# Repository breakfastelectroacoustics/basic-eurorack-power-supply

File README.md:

# Basic Eurorack Power Supply

This power supply derives +12 V, -12 V and +5 V from 12 V AC. It is intended as a cheap and simple bipolar (plus 5 V) power supply for modular synthesizers and general test setups.

The double-sided PCB layout is very straightforward. One of the AC inputs connected on the left will be referenced as GND. The regulated DC output on the right will be relative to this reference.

To keep it as simple as possible the circuit only contains essential components. 7812, 7912 and 7805 linear regulators are used in their basic fixed-voltage configuration (as suggested in the datasheets and used in many designs e.g. from [MFOS](http://musicfromouterspace.com/analogsynth_new/WALLWARTSUPPLY/WALLWARTSUPPLY.php) and [ModularSynth.ru](http://www.modularsynth.ru/en/diy/low_cost_psu/)).

The diodes, voltage regulators and the AC supply used determine the amount of current this power supply can provide. Depending on the application additional fuses or protection diodes are recommended. If heatsinks are used on the linear regulators, they must not touch each other.

Components listed on the BOM are only loosely defined. They have to be specified/adapted to fit individual requirements (with preferably generous safety margins, e.g. capacitors rated 35 V for 12-15 V AC input).

Dimensions: 99.06 x 41.91 mm

Mounting hole pattern: 50.8 (25.4) x 35.56 mm (~3 mm hole diameter)

The PCB files are licensed under a [Creative Commons Attribution-NonCommercial-ShareAlike 4.0 International License](https://creativecommons.org/licenses/by-nc-sa/4.0/).

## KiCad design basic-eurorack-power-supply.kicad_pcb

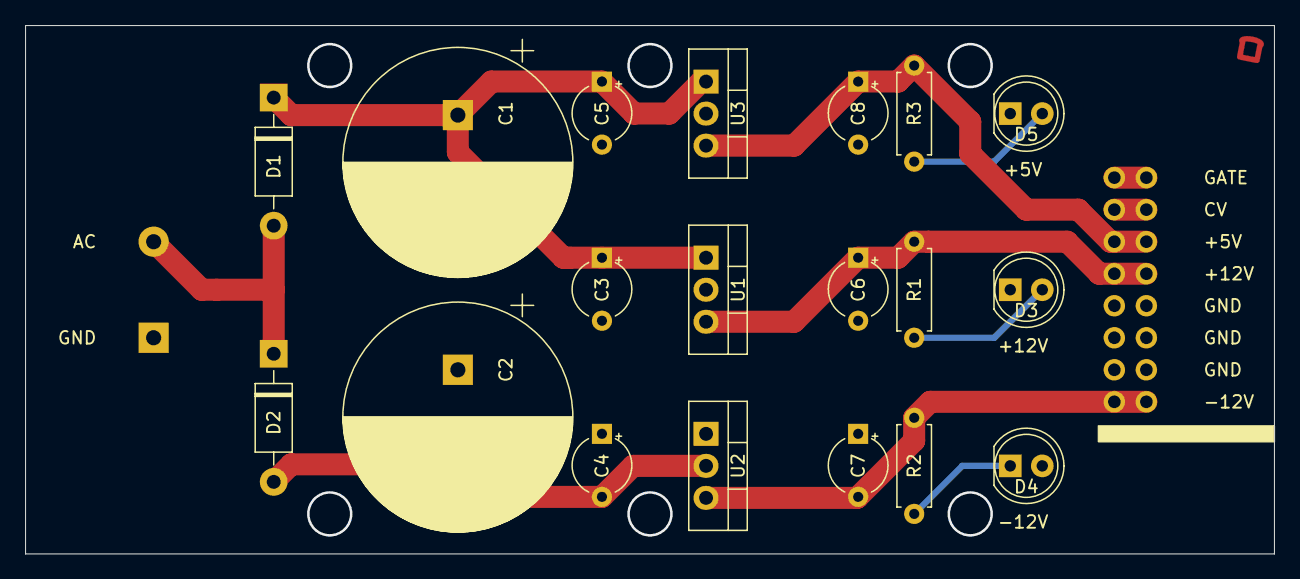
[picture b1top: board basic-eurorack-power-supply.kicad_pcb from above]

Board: 2 copper layers, 99.1 x 41.9 mm, 19 parts (0 on the bottom side), 10 nets.

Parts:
C1, C2: 4700u; CP_Radial_D18.0mm_P7.50mm
C3, C4, C5, C6, C7, C8: 1u; CP_Radial_Tantal_D4.5mm_P5.00mm
D1, D2: 1N4001; D_DO-41_SOD81_P10.16mm_Horizontal
D3, D4, D5: LED; LED_D5.0mm
R1, R2, R3: R; R_Axial_DIN0207_L6.3mm_D2.5mm_P7.62mm_Horizontal
U1: L7812; TO-220-3_Vertical
U2: L7912; TO-220-3_Vertical
U3: L7805; TO-220-3_Vertical

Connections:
+5V: C8.1, R3.1, U3.3
+12V: C6.1, R1.2, U1.3
-12V: C7.2, R2.2, U2.3
AC: D1.2, D2.1
GND: C1.2, C2.1, C3.2, C4.1, C5.2, C6.2, C7.1, C8.2, D3.1, D4.2, D5.1, U1.2, U2.1, U3.2
unnamed: C1.1, C3.1, C5.1, D1.1, U1.1, U3.1
unnamed: C2.2, C4.2, D2.2, U2.2
unnamed: D3.2, R1.1
unnamed: D4.1, R2.1
unnamed: D5.2, R3.2

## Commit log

2021-03-11 Add Photos
2021-05-20 Update BOM
